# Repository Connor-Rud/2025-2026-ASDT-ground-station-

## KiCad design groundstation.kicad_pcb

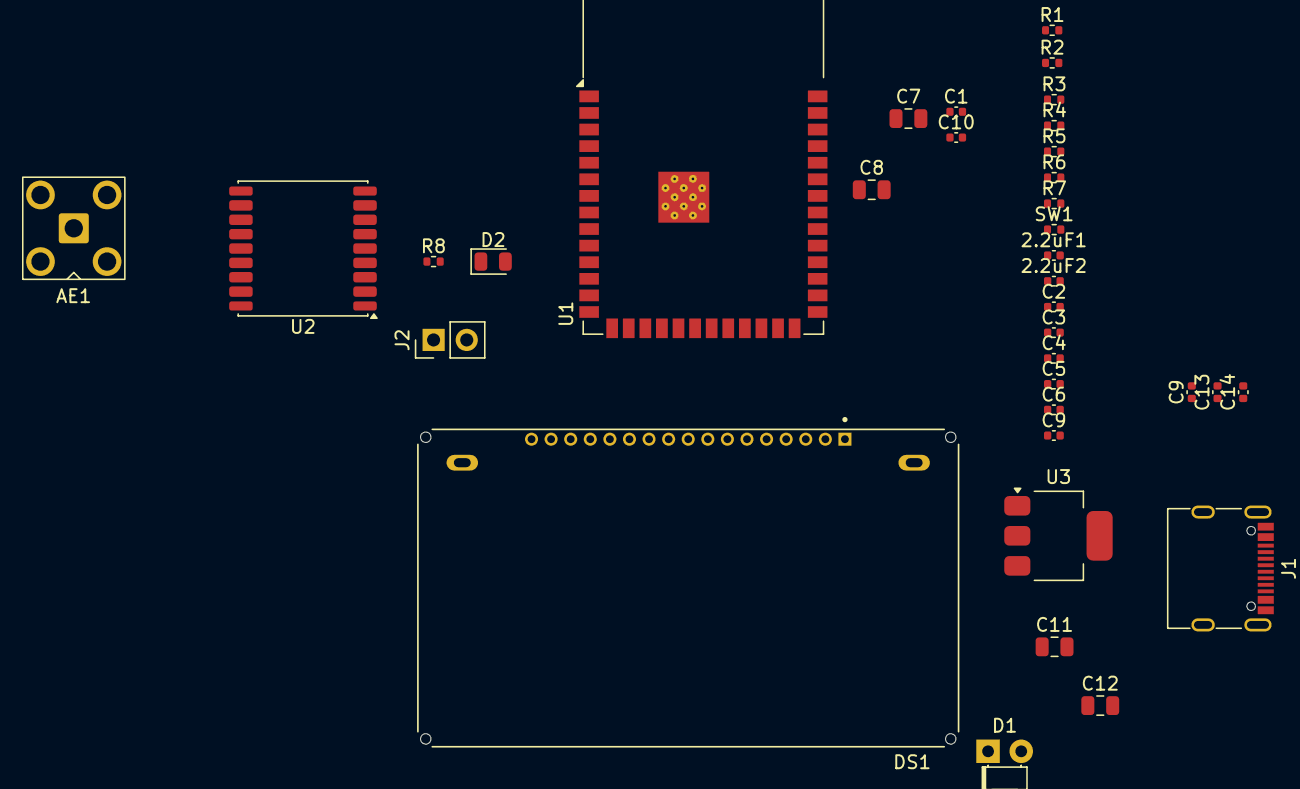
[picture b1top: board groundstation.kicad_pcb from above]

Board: 2 copper layers, 35 parts (0 on the bottom side), 33 nets, no tracks yet.

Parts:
2.2uF1, 2.2uF2: C_Small_US; C_0402_1005Metric
AE1: Antenna; SMA_BAT_Wireless_BWSMA-KWE-Z001
C1: 0.1u; C_0402_1005Metric
C2: 2.2u; C_0402_1005Metric
C3, C4, C6, C9, C10: 1u; C_0402_1005Metric
C5: 1.0u; C_0402_1005Metric
C7: 10uF; C_0805_2012Metric
C8: 0.1u; C_0805_2012Metric
C9#2, C13, C14: 2.2uF; C_0402_1005Metric
C11: 22u; C_0805_2012Metric
C12: 10u; C_0805_2012Metric
D1: LED; LED_D1.8mm_W1.8mm_H2.4mm_Horizontal_O1.27mm_Z1.6mm
D2: LED; LED_0805_2012Metric
DS1: NHD-C12832A1Z-FSW-FBW-3V3; LCD_NHD-C12832A1Z-FSW-FBW-3V3
J1: USB_C_Receptacle_USB2.0_16P; USB_C_Receptacle_G-Switch_GT-USB-7010ASV
J2: Conn_01x02_Pin; PinHeader_1x02_P2.54mm_Vertical
R1, R2: 22; R_0402_1005Metric
R3, R4: 5.1k; R_0402_1005Metric
R5: 0; R_0402_1005Metric
R6: 410; R_0402_1005Metric
R7: 10k; R_0402_1005Metric
R8: 1k; R_0402_1005Metric
SW1: SW_Push; R_0402_1005Metric
U1: ESP32-S3-WROOM-1
U2: MAX-M10S; ublox_MAX
U3: AMS1117-3.3; SOT-223-3_TabPin2

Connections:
5V: C12.1, J1.A4 (VBUS), J1.A9 (VBUS), J1.B4 (VBUS), J1.B9 (VBUS), U3.3 (VI)
+3V3: C7.1, C8.1, C11.1, D1.2 (A), D2.2 (A), DS1.12 (VDD), DS1.A (LED+), R7.2, U1.2 (3V3), U2.7 (VCC_IO), U2.8 (VCC), U3.2 (VO)
/EXTINT: U1.5 (IO5), U2.5 (EXTINT)
Display_A0: DS1.15 (A0), U1.15 (IO3)
Display_CS1: DS1.17 (~CS1), U1.39 (IO1)
Display_RST: DS1.16 (~RST), U1.38 (IO2)
Display_SI: DS1.13 (SI), U1.4 (IO4)
EN: C10.2, R5.2, R7.1, U1.3 (EN)
GND: C1.1, C2.2, C3.2, C4.2, C5.2, C6.2, C7.2, C8.2, C9.2, C10.1, C11.2, C12.2, DS1.11 (VSS), DS1.K (LED-), J1.A1 (GND), J1.A12 (GND), J1.B1 (GND), J1.B12 (GND), J1.S1 (SHIELD), J2.2, R3.1, R4.1, R6.1, SW1.1, U1.1 (GND), U1.40 (GND), U1.41 (GND), U2.1 (GND), U2.10 (GND), U2.12 (GND), U3.1 (GND)
unnamed: AE1.1 (A), U2.11 (RF_IN)
unnamed: C1.2, R5.1, SW1.2
unnamed: D1.1 (K), R6.2
unnamed: D2.1 (K), R8.1
unnamed: 2.2uF1.1, C14.1, DS1.8 (C1+)
unnamed: 2.2uF1.2, C14.2, DS1.9 (C1-)
unnamed: 2.2uF2.1, C13.1, DS1.7 (C2+)
unnamed: 2.2uF2.2, C13.2, DS1.6 (C2-)
unnamed: C9.1, DS1.1 (V0)
unnamed: C6.1, DS1.2 (V1)
unnamed: C5.1, DS1.3 (V2)
unnamed: C4.1, DS1.4 (V3)
unnamed: C3.1, DS1.5 (V4)
unnamed: C2.1, DS1.10 (VOUT)
unnamed: J1.A5 (CC1), R3.2
unnamed: J1.B5 (CC2), R4.2
unnamed: J1.A6 (D+), J1.B6 (D+), R2.2
unnamed: J1.A7 (D-), J1.B7 (D-), R1.2
unnamed: J2.1, U1.27 (IO0)
unnamed: R2.1, U1.14 (USB_D+)
unnamed: R1.1, U1.13 (USB_D-)
unnamed: R8.2, U2.4 (TIMEPULSE)
SCL: DS1.14 (SCL), U1.22 (IO14), U2.17 (SCL)
SDA: U1.21 (IO13), U2.16 (SDA)

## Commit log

2026-01-17 Initial Kicad upload to git
2026-01-17 usb setup
2026-01-18 removed temporary files
2026-02-02 Add .zip files to .gitignore
2026-02-02 added display receptacle port for 7in TFT
2026-02-02 Update schematicand PCB
2026-02-02 Remove KiCad autosaves and backups from version control
2026-02-14 done with schematic (hopefully)
2026-02-21 added GPS module
2026-02-28 dunno, random adds
